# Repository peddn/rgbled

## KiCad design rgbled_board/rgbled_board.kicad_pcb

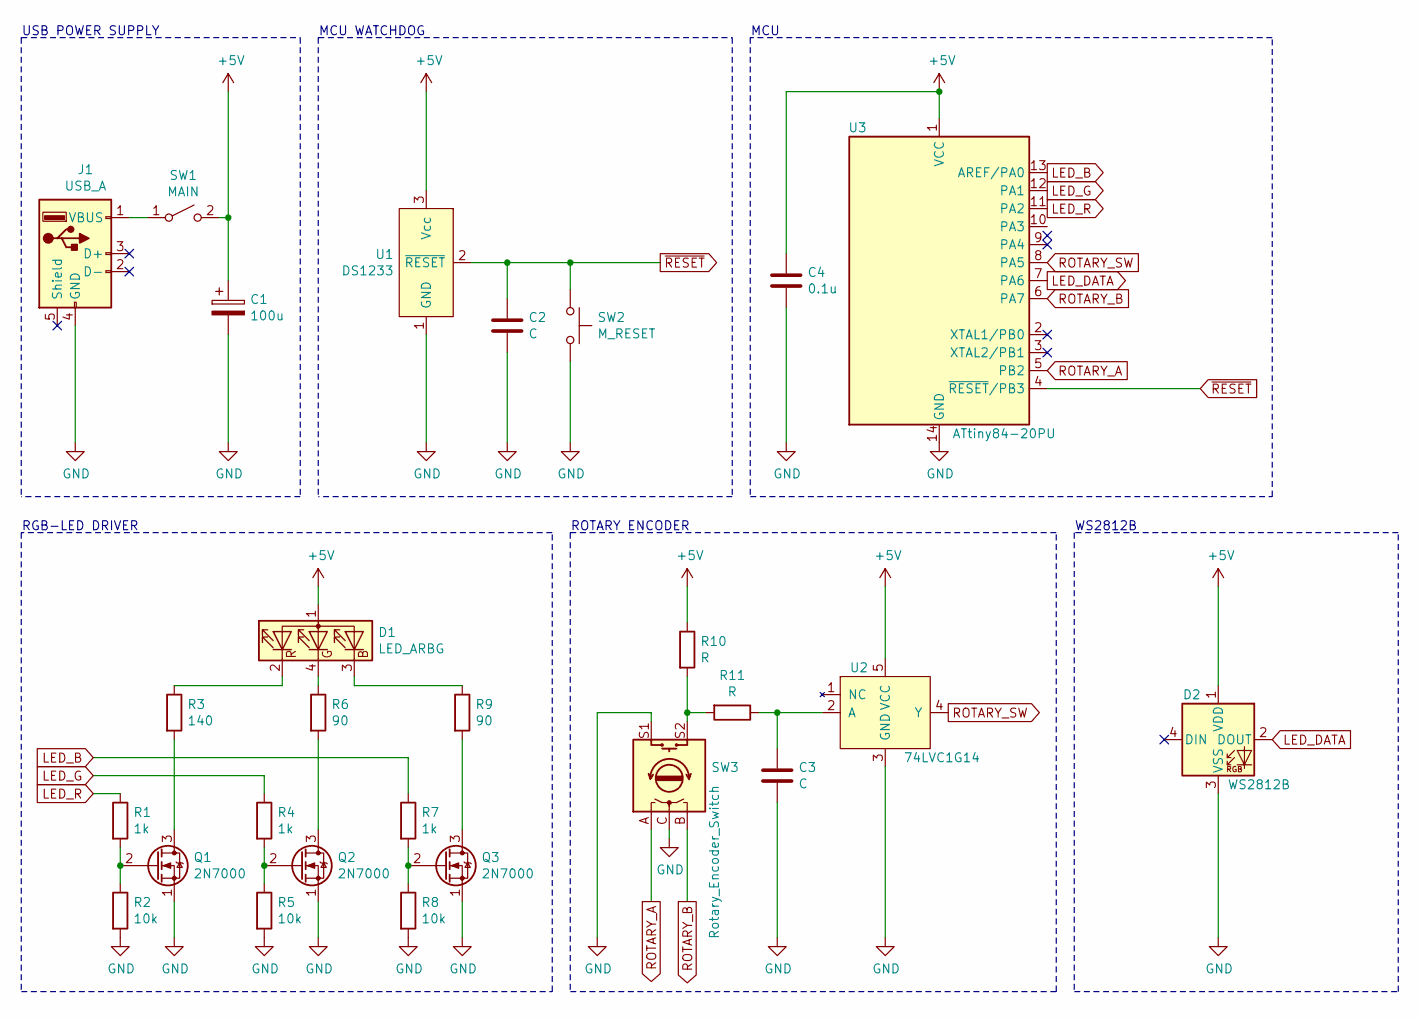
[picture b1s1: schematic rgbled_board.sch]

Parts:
C1: 100u; CP_Radial_D6.3mm_P2.50mm
C2, C3: C; C_Disc_D5.0mm_W2.5mm_P5.00mm
C4: 0.1u; C_Disc_D5.0mm_W2.5mm_P5.00mm
D1: LED_ARBG; JST_XH_S4B-XH-A_1x04_P2.50mm_Horizontal
D2: WS2812B; JST_XH_S3B-XH-A_1x03_P2.50mm_Horizontal
J1: USB_A
Q1, Q2, Q3: 2N7000; TO-92_Inline
R1, R4, R7: 1k; R_Axial_DIN0207_L6.3mm_D2.5mm_P10.16mm_Horizontal
R2, R5, R8: 10k; R_Axial_DIN0207_L6.3mm_D2.5mm_P10.16mm_Horizontal
R3: 140; R_Axial_DIN0207_L6.3mm_D2.5mm_P10.16mm_Horizontal
R6, R9: 90; R_Axial_DIN0207_L6.3mm_D2.5mm_P10.16mm_Horizontal
R10, R11: R; R_Axial_DIN0207_L6.3mm_D2.5mm_P10.16mm_Horizontal
SW1: MAIN; JST_XH_S2B-XH-A_1x02_P2.50mm_Horizontal
SW2: M_RESET; SW_PUSH_6mm_H5mm
SW3: Rotary_Encoder_Switch; JST_XH_5PIN_HORIZONTAL_ROTARY_ENCODER
U1: DS1233; TO-92_Inline
U2: 74LVC1G14; SOT-23-5
U3: ATtiny84-20PU; DIP-14_W7.62mm

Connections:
+5V: C1.1, C4.1, D1.1 (A), D2.1 (VDD), R10.1, SW1.2 (B), U1.3 (Vcc), U2.5 (VCC), U3.1 (VCC)
GND: C1.2, C2.2, C3.1, C4.2, D2.3 (VSS), J1.4 (GND), Q1.1 (S), Q2.1 (S), Q3.1 (S), R2.2, R5.2, R8.2, SW2.2, SW3.C, SW3.S1, U1.1 (GND), U2.3 (GND), U3.14 (GND)
LED_B: R7.1, U3.13 (AREF/PA0)
LED_DATA: D2.2 (DOUT), U3.7 (PA6)
LED_G: R4.1, U3.12 (PA1)
LED_R: R1.1, U3.11 (PA2)
unnamed: C3.2, R11.1, U2.2 (A)
unnamed: D1.2 (RK), R3.1
unnamed: D1.3 (BK), R9.1
unnamed: D1.4 (GK), R6.1
unnamed: J1.1 (VBUS), SW1.1 (A)
unnamed: Q1.2 (G), R1.2, R2.1
unnamed: Q1.3 (D), R3.2
unnamed: Q2.2 (G), R4.2, R5.1
unnamed: Q2.3 (D), R6.2
unnamed: Q3.2 (G), R7.2, R8.1
unnamed: Q3.3 (D), R9.2
unnamed: R10.2, R11.2, SW3.S2
ROTARY_A: SW3.A, U3.5 (PB2)
ROTARY_B: SW3.B, U3.6 (PA7)
ROTARY_SW: U2.4 (Y), U3.8 (PA5)
~RESET: C2.1, SW2.1, U1.2 (~RESET), U3.4 (~RESET~/PB3)

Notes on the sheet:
RGB-LED DRIVER
MCU
ROTARY ENCODER
WS2812B
USB POWER SUPPLY
MCU WATCHDOG

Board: 2 copper layers, 26 parts (0 on the bottom side), 21 nets, no tracks yet.
